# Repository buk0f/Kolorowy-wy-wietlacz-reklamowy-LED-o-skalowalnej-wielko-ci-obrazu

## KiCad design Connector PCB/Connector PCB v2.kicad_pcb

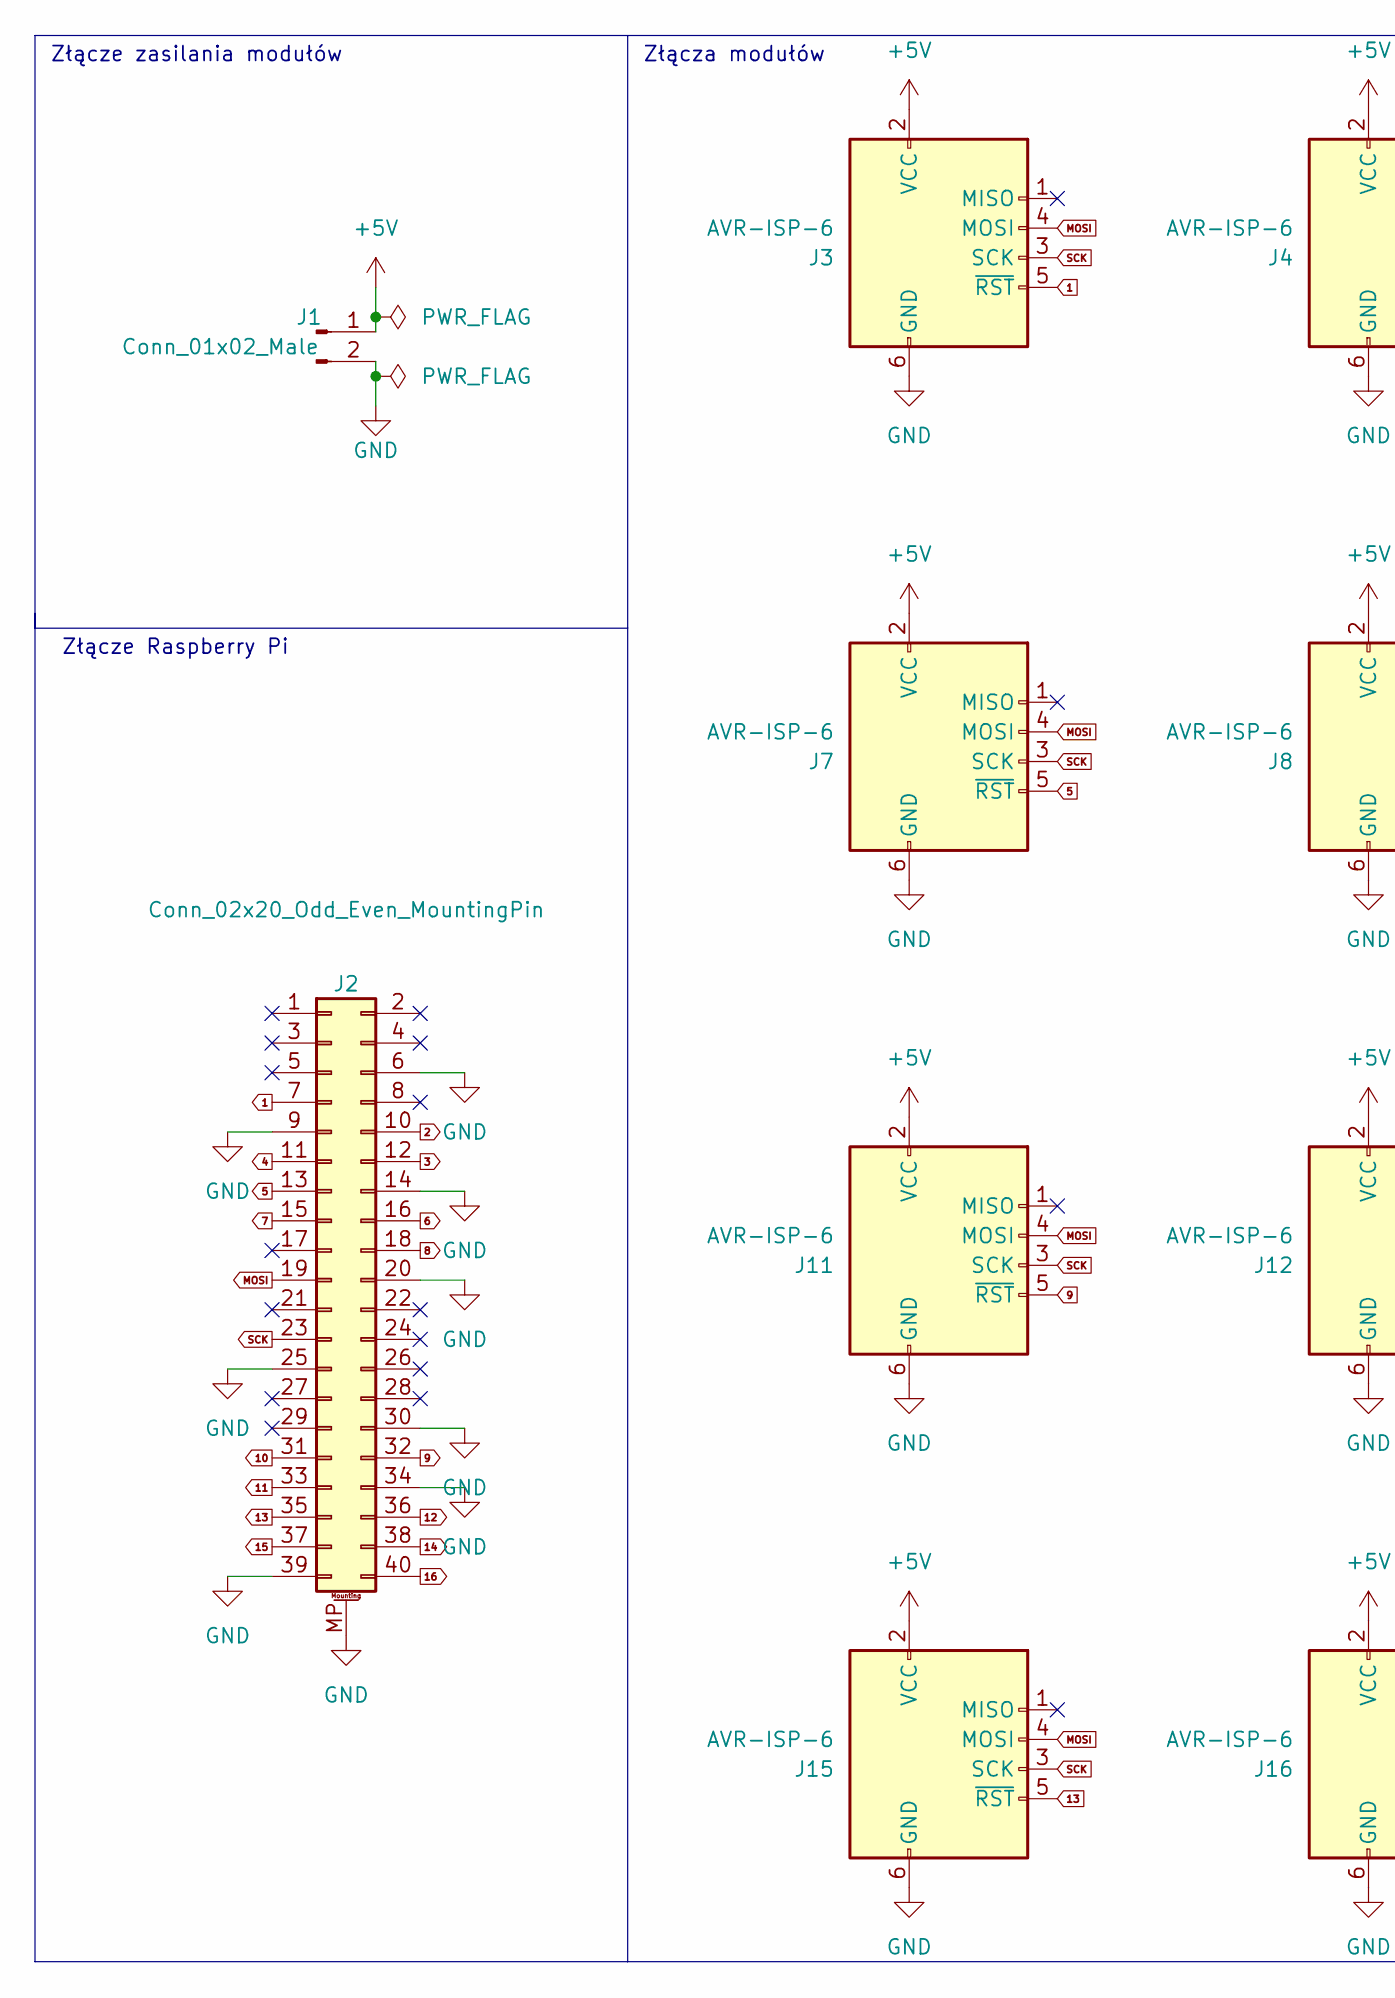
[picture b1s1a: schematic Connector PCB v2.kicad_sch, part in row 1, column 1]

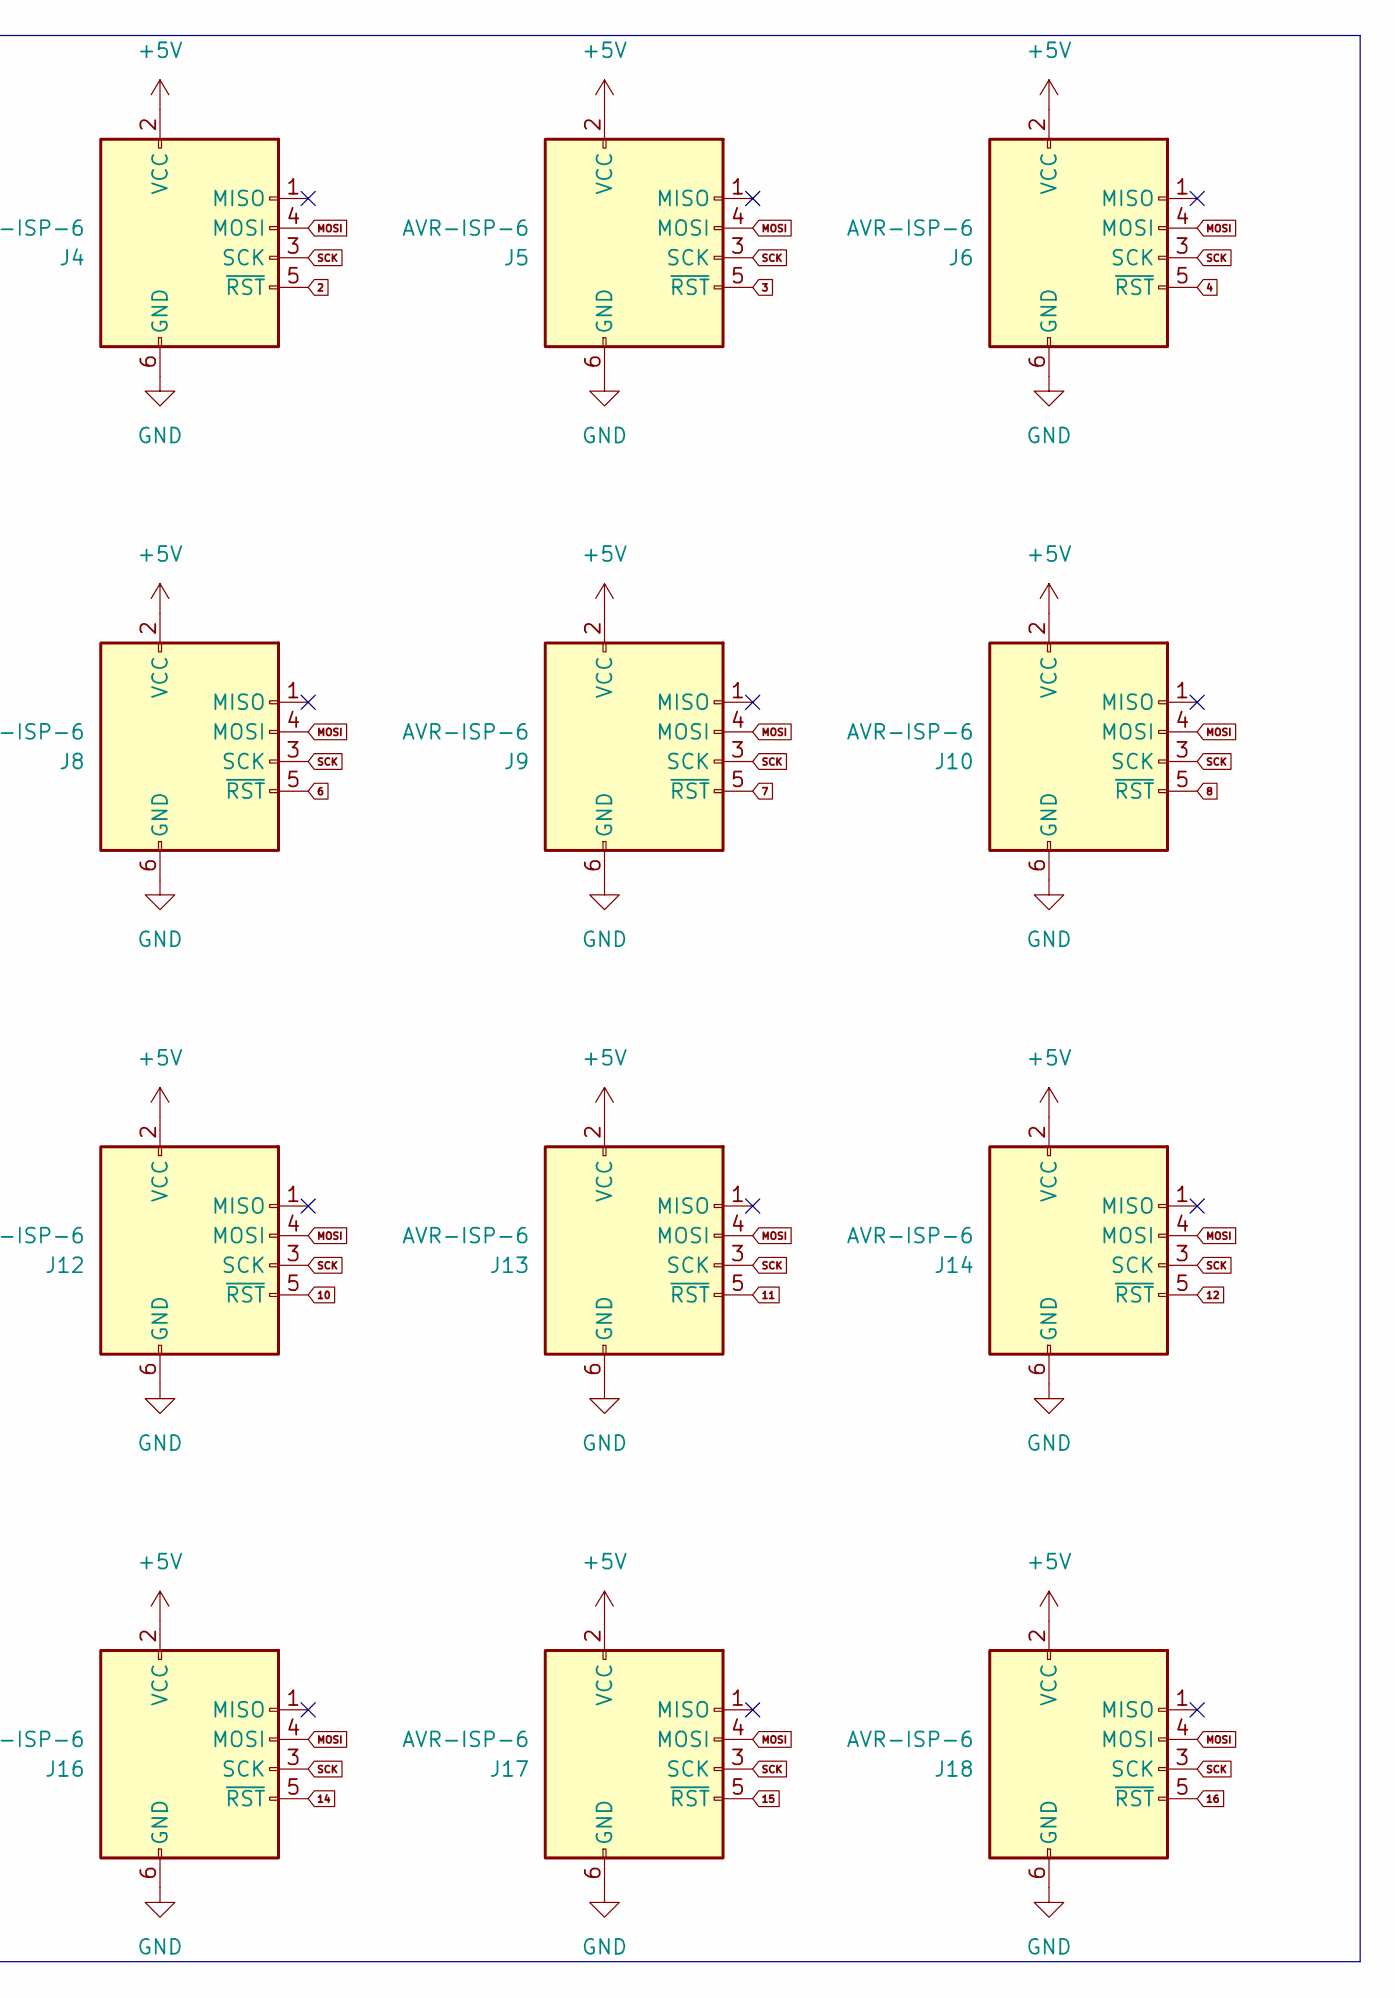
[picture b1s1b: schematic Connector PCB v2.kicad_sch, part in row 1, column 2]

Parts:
J1: Conn_01x02_Male; JWT_A3963_1x02_P3.96mm_Vertical
J2: Conn_02x20_Odd_Even_MountingPin; IDC-Header_2x20-1MP_P2.54mm_Latch6.5mm_Vertical
J3, J4, J5, J6, J7, J8, J9, J10, J11, J12, J13, J14, J15, J16, J17, J18: AVR-ISP-6; IDC-Header_2x03_P2.54mm_Vertical

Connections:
1: J2.7, J3.5 (~RST)
2: J2.10, J4.5 (~RST)
3: J2.12, J5.5 (~RST)
4: J2.11, J6.5 (~RST)
5: J2.13, J7.5 (~RST)
6: J2.16, J8.5 (~RST)
7: J2.15, J9.5 (~RST)
8: J2.18, J10.5 (~RST)
9: J2.32, J11.5 (~RST)
10: J2.31, J12.5 (~RST)
11: J2.33, J13.5 (~RST)
12: J2.36, J14.5 (~RST)
13: J2.35, J15.5 (~RST)
14: J2.38, J16.5 (~RST)
15: J2.37, J17.5 (~RST)
16: J2.40, J18.5 (~RST)
+5V: J1.1, J3.2 (VCC), J4.2 (VCC), J5.2 (VCC), J6.2 (VCC), J7.2 (VCC), J8.2 (VCC), J9.2 (VCC), J10.2 (VCC), J11.2 (VCC), J12.2 (VCC), J13.2 (VCC), J14.2 (VCC), J15.2 (VCC), J16.2 (VCC), J17.2 (VCC), J18.2 (VCC)
GND: J1.2, J2.6, J2.9, J2.14, J2.20, J2.25, J2.30, J2.34, J2.39, J2.MP (MountPin), J3.6 (GND), J4.6 (GND), J5.6 (GND), J6.6 (GND), J7.6 (GND), J8.6 (GND), J9.6 (GND), J10.6 (GND), J11.6 (GND), J12.6 (GND), J13.6 (GND), J14.6 (GND), J15.6 (GND), J16.6 (GND), J17.6 (GND), J18.6 (GND)
MOSI: J2.19, J3.4 (MOSI), J4.4 (MOSI), J5.4 (MOSI), J6.4 (MOSI), J7.4 (MOSI), J8.4 (MOSI), J9.4 (MOSI), J10.4 (MOSI), J11.4 (MOSI), J12.4 (MOSI), J13.4 (MOSI), J14.4 (MOSI), J15.4 (MOSI), J16.4 (MOSI), J17.4 (MOSI), J18.4 (MOSI)
SCK: J2.23, J3.3 (SCK), J4.3 (SCK), J5.3 (SCK), J6.3 (SCK), J7.3 (SCK), J8.3 (SCK), J9.3 (SCK), J10.3 (SCK), J11.3 (SCK), J12.3 (SCK), J13.3 (SCK), J14.3 (SCK), J15.3 (SCK), J16.3 (SCK), J17.3 (SCK), J18.3 (SCK)

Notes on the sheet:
Złącze zasilania modułów
Złącze Raspberry Pi
Złącza modułów

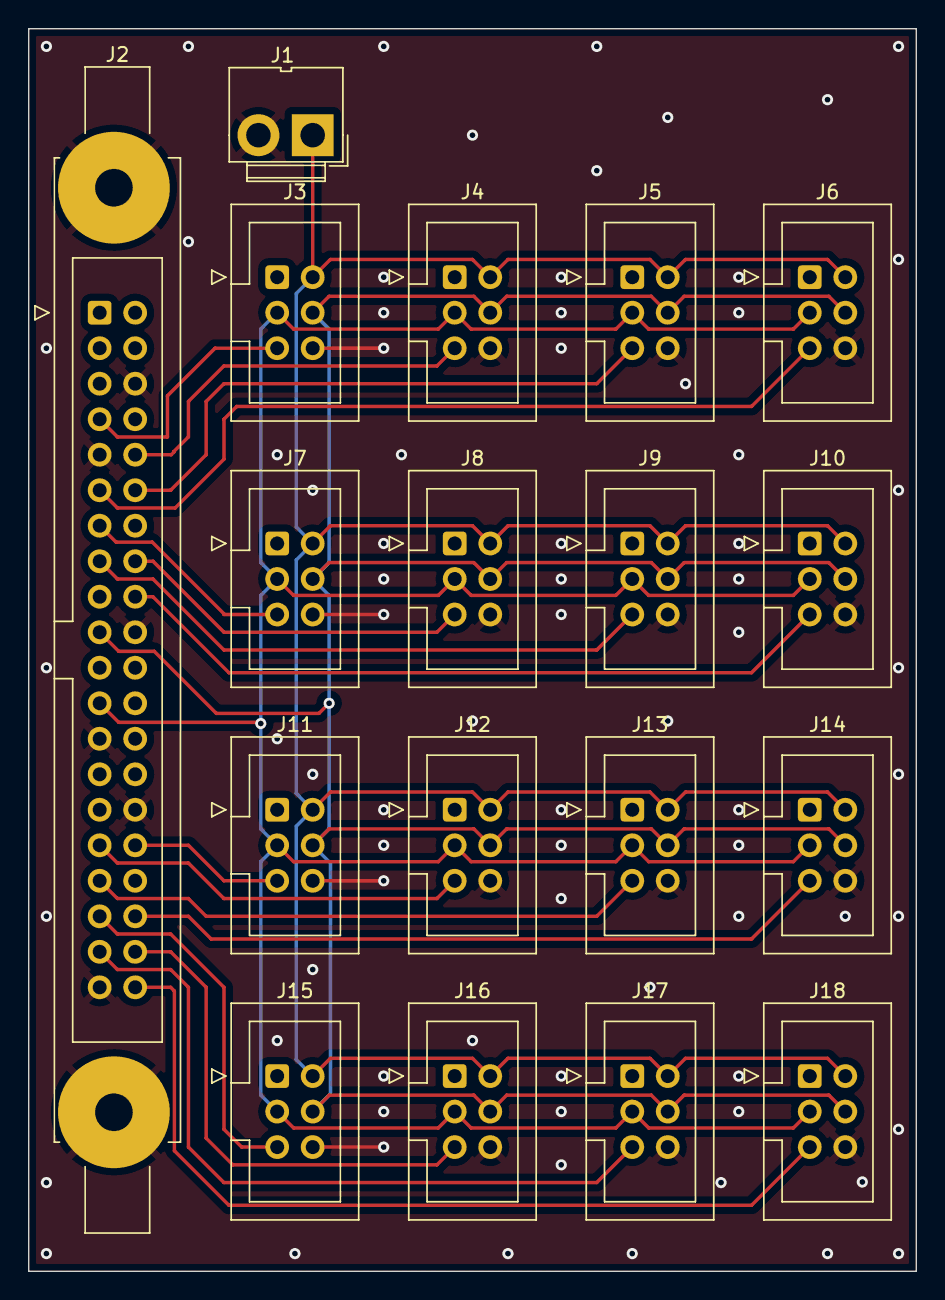
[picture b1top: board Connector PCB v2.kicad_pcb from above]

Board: 2 copper layers, 63.5 x 88.9 mm, 18 parts (0 on the bottom side), 20 nets.

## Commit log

2022-06-24 Added firmware, PCB design for LED Module
2022-06-24 moved folders
2022-06-27 Add files via upload
    Schematic and PCB Layout can be opened KiCAD 6.0 or newer.
2022-06-27 Rename SSACLD-1.3.2-FINAL.py to Connector PCB/SSACLD-1.3.2-FINAL.py
